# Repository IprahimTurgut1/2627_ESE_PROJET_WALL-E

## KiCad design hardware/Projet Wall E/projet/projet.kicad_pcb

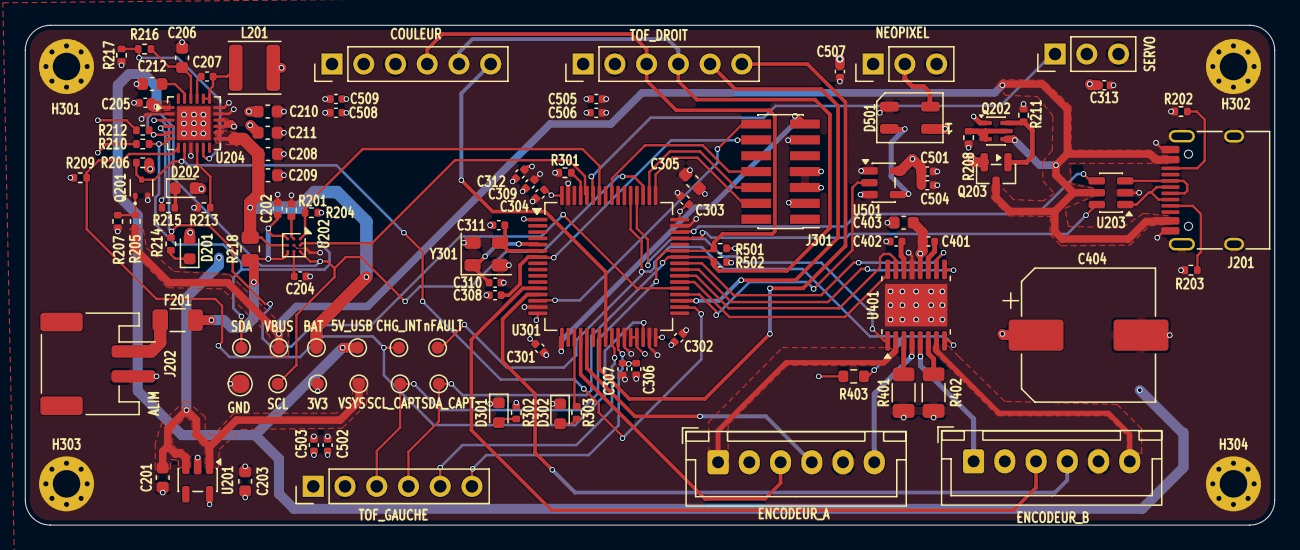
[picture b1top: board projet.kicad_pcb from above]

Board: 4 copper layers, 100.0 x 40.0 mm, 108 parts (0 on the bottom side), 75 nets.

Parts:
3V3: +3.3V; TestPoint_Pad_D1.0mm
5V_USB: +5V_USB; TestPoint_Pad_D1.0mm
BAT: BAT; TestPoint_Pad_D1.0mm
C201, C203, C208, C209, C210, C211, C212, C403: 10u; C_0603_1608Metric
C202, C205, C307, C312, C313: 1u; C_0402_1005Metric
C204: 2u2; C_0402_1005Metric
C206, C305: 4u7; C_0603_1608Metric
C207: 47n; C_0402_1005Metric
C301, C302, C303, C304, C308, C309, C501, C504, C507: 100n; C_0402_1005Metric
C306, C401: 10n; C_0402_1005Metric
C310, C311: 10p; C_0402_1005Metric
C402: 2.2uF; C_0402_1005Metric
C404: 470u/25V; CP_Elec_10x10.5
C502, C505, C508: 100nF; C_0402_1005Metric
C503, C506, C509: 10uF; C_0402_1005Metric
CHG_INT: CHG_INT; TestPoint_Pad_D1.0mm
COULEUR: Conn_01x06; PinHeader_1x06_P2.54mm_Vertical
D201, D202: LED; LED_0603_1608Metric
D301: POWER; LED_0603_1608Metric
D302: STATUS; LED_0603_1608Metric
D501: WS2812B; LED_WS2812B-Mini_PLCC4_3.5x3.5mm
ENCODEUR_A: Conn_01x06; JST_XH_B6B-XH-A_1x06_P2.50mm_Vertical
ENCODEUR_B: Conn_01x06; JST_XH_B6B-XH-A_1x06_P2.50mm_Vertical
F201: Fuse; Fuse_1206_3216Metric
GND: GND; TestPoint_Pad_D1.5mm
H301, H302, H303, H304: MountingHole_Pad; MountingHole_2.2mm_M2_Pad_Via
J201: USB_C_Receptacle_USB2.0_16P; USB_C_Receptacle_HRO_TYPE-C-31-M-12
J202: Conn_01x02; JST_PH_S2B-PH-SM4-TB_1x02-1MP_P2.00mm_Horizontal
J301: Conn_ST_STDC14; PinHeader_2x07_P1.27mm_Vertical_SMD
L201: 1u; L_Sunlord_SWPA4030S
NEOPIXEL: Conn_01x03; PinHeader_1x03_P2.54mm_Vertical
Q201: 2SK3019; SOT-523
Q202: MMDT5401; SOT-363_SC-70-6
Q203: DMP3099L; SOT-23
R201, R204, R206, R207, R216, R217, R301: 10k; R_0402_1005Metric
R202, R203: 5k1; R_0402_1005Metric
R205: 100; R_0402_1005Metric
R208, R211: 100k; R_0402_1005Metric
R209: 4k7; R_0402_1005Metric
R210, R212: 1.5k; R_0402_1005Metric
R213: 470; R_0402_1005Metric
R214, R215: 2k2; R_0402_1005Metric
R218: 10m; R_0805_2012Metric
R302, R303: 1k; R_0402_1005Metric
R401, R402: 200m; R_1206_3216Metric
R403: 10k; R_0603_1608Metric
R501, R502: 4.7k; R_0402_1005Metric
SCL: SCL; TestPoint_Pad_D1.0mm
SCL_CAPT: SCL_CAPT; TestPoint_Pad_D1.0mm
SDA: SDA; TestPoint_Pad_D1.0mm
SDA_CAPT: SDA_CAPT; TestPoint_Pad_D1.0mm
SERVO: Conn_01x03; PinHeader_1x03_P2.54mm_Vertical
TOF_DROIT: Conn_01x06; PinHeader_1x06_P2.54mm_Vertical
TOF_GAUCHE: Conn_01x06; PinHeader_1x06_P2.54mm_Vertical
U201: AP2112K-3.3; SOT-23-5
U202: BQ27220YZFR; Texas_DSBGA-9_1.62x1.58mm_Layout3x3_P0.5mm
U203: USBLC6-2SC6; SOT-23-6
U204: BQ25896RTW; Texas_RTW_WQFN-24-1EP_4x4mm_P0.5mm_EP2.7x2.7mm_ThermalVias
U301: STM32G431RBTx; LQFP-64_10x10mm_P0.5mm
U401: DRV8833PWP; HTSSOP-16-1EP_4.4x5mm_P0.65mm_EP3.4x5mm_Mask2.46x2.31mm_The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
U501: SN74AHCT1G125DBVR; SOT-23-5
VBUS: VBUS; TestPoint_Pad_D1.0mm
VSYS: VSYS; TestPoint_Pad_D1.0mm
Y301: 16MHz; Crystal_SMD_EuroQuartz_MT-4Pin_3.2x2.5mm
nFAULT: MOT_nFAULT; TestPoint_Pad_D1.0mm

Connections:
+3.3V: 3V3.1 (1_1), C203.1, C301.1, C302.1, C303.1, C304.1, C305.1, C306.1, C307.1, C309.1, C312.1, C502.1, C503.1, C505.1, C506.1, C508.1, C509.1, COULEUR.1, ENCODEUR_A.2, ENCODEUR_B.2, J301.3 (VCC), R204.2, R209.1, R210.1, R212.1, R302.1, R403.2, R501.1, R502.1, TOF_DROIT.1, TOF_GAUCHE.1, U201.5 (VOUT), U301.1 (VBAT), U301.16 (VDD), U301.28 (VREF+), U301.29 (VDDA), U301.32 (VDD), U301.48 (VDD), U301.64 (VDD)
+5V_USB: 5V_USB.1 (1_1), C205.1, C313.1, C401.1, C403.1, C404.1, C501.1, C504.2, C507.1, D501.1 (VDD), NEOPIXEL.1, Q202.1 (E1), Q203.2 (S), SERVO.2, U204.1 (VBUS), U401.12 (VM), U501.5 (VCC)
/Alimentation/BAT: BAT.1 (1_1), C208.2, C209.2, R218.2, U202.C2 (SRN), U204.13 (BAT), U204.14 (BAT)
/Alimentation/CHG_INT: CHG_INT.1 (1_1), R209.2, U204.7 (INT), U301.30 (PB10)
/Alimentation/CHG_OTG: Q201.3 (D), R206.2, U204.8 (OTG), U301.34 (PB12)
/Alimentation/CHG_PG: R214.2, U204.3 (~PG), U301.37 (PB15)
/Alimentation/GAUGE_INT: R204.1, U202.A1 (GPOUT), U301.58 (PB5)
/Alimentation/PACKP: C202.1, F201.1, R218.1, U202.C1 (SRP), U202.C3 (BAT)
/Alimentation/SCL: R212.2, SCL.1 (1_1), U202.A3 (SCL), U204.5 (SCL), U301.51 (PA15)
/Alimentation/SDA: R210.2, SDA.1 (1_1), U202.A2 (SDA), U204.6 (SDA), U301.60 (PB7)
/Alimentation/USB_DM: U203.6 (I/O1), U301.45 (PA11)
/Alimentation/USB_DP: U203.4 (I/O2), U301.46 (PA12)
/Capteur/APDS_INT: COULEUR.6, U301.24 (PB0)
/Capteur/NEOPIXEL: U301.36 (PB14), U501.2
/Capteur/NP_5V: D501.4 (DIN), U501.4
/Capteur/SCL_CAPT: COULEUR.4, R501.2, SCL_CAPT.1 (1_1), TOF_DROIT.3, TOF_GAUCHE.3, U301.43 (PA9)
/Capteur/SDA_CAPT: COULEUR.5, R502.2, SDA_CAPT.1 (1_1), TOF_DROIT.4, TOF_GAUCHE.4, U301.42 (PA8)
/Capteur/TOF_L_GPIO1: TOF_GAUCHE.5, U301.25 (PB1)
/Capteur/TOF_L_XSHUT: TOF_GAUCHE.6, U301.26 (PB2)
/Capteur/TOF_R_GPIO1: TOF_DROIT.5, U301.35 (PB13)
/Capteur/TOF_R_XSHUT: TOF_DROIT.6, U301.23 (PC5)
/MCU/BOOT0: R301.2, U301.61 (PB8)
/MCU/ENCA_AOUT: ENCODEUR_A.3, U301.20 (PA6)
/MCU/ENCA_BOUT: ENCODEUR_B.3, U301.12 (PA0)
/MCU/ENCB_AOUT: ENCODEUR_A.4, U301.21 (PA7)
/MCU/ENCB_BOUT: ENCODEUR_B.4, U301.13 (PA1)
/MCU/LED_STATUS: R303.1, U301.19 (PA5)
/MCU/MOT_AIN1: U301.38 (PC6), U401.16 (AIN1)
/MCU/MOT_AIN2: U301.39 (PC7), U401.15 (AIN2)
/MCU/MOT_BIN1: U301.40 (PC8), U401.9 (BIN1)
/MCU/MOT_BIN2: U301.41 (PC9), U401.10 (BIN2)
/MCU/MOT_nFAULT: R403.1, U301.53 (PC11), U401.8 (~FAULT), nFAULT.1 (1_1)
/MCU/MOT_nSLEEP: U301.52 (PC10), U401.1 (~SLEEP)
/MCU/NRST: C308.1, J301.12 (~RST), U301.7 (PG10)
/MCU/SERVO_PWM: SERVO.1, U301.59 (PB6)
/MCU/SWCLK: J301.6 (JCLK/SWCLK), U301.50 (PA14)
/MCU/SWDIO: J301.4 (JTMS/SWDIO), U301.49 (PA13)
/MCU/SWO: J301.8 (JTDO/SWO), U301.56 (PB3)
/MCU/VCP_RX: J301.13 (VCP_RX), U301.17 (PA3)
/MCU/VCP_TX: J301.14 (VCP_TX), U301.14 (PA2)
/Moteur/AOUT1: ENCODEUR_A.1, U401.2 (AOUT1)
/Moteur/AOUT2: ENCODEUR_A.6, U401.4 (AOUT2)
/Moteur/BOUT1: ENCODEUR_B.6, U401.7 (BOUT1)
/Moteur/BOUT2: ENCODEUR_B.1, U401.5 (BOUT2)
GND: C201.2, C202.2, C203.2, C204.2, C205.2, C206.1, C208.1, C209.1, C210.1, C211.1, C212.1, C301.2, C302.2, C303.2, C304.2, C305.2, C306.2, C307.2, C308.2, C309.2, C310.1, C311.1, C312.2, C313.2, C402.1, C403.2, C404.2, C501.2, C502.2, C503.2, C504.1, C505.2, C506.2, C507.2, C508.2, C509.2, COULEUR.3, D301.1 (K), D302.1 (K), D501.3 (VSS), ENCODEUR_A.5, ENCODEUR_B.5, GND.1 (1_1), H301.1 (1_1), H302.1 (1_1), H303.1 (1_1), H304.1 (1_1), J201.A1 (GND), J201.A12 (GND), J201.B1 (GND), J201.B12 (GND), J201.SH (SHIELD), J202.2, J301.5 (GND), J301.7 (GND), J301.11 (GNDDetect), NEOPIXEL.3, Q201.2 (S), R201.2, R202.2, R203.2, R207.2, R208.2, R211.2, R213.2, R217.2, R301.1, R401.1, R402.1, SERVO.3, TOF_DROIT.2, TOF_GAUCHE.2, U201.2 (GND), U202.B2 (V_{SS}), U203.2 (GND), U204.2 (PSEL), U204.9 (~CE), U204.17 (PGND), U204.18 (PGND), U204.25 (PGND), U301.15 (VSS), U301.27 (VSSA), U301.31 (VSS), U301.47 (VSS), U301.63 (VSS), U401.13 (GND), U401.17 (GND), U501.1, U501.3 (GND), Y301.2 (G), Y301.4 (G)
unnamed: C207.2, L201.1, U204.19 (SW), U204.20 (SW)
unnamed: D201.1 (K), R214.1
unnamed: D202.1 (K), R215.1
unnamed: D301.2 (A), R302.2
unnamed: D302.2 (A), R303.2
unnamed: D501.2 (DOUT), NEOPIXEL.2
unnamed: J201.A5 (CC1), R203.1
unnamed: J201.B5 (CC2), R202.1
unnamed: J201.A6 (D+), J201.B6 (D+), U203.3 (I/O2)
unnamed: J201.A7 (D-), J201.B7 (D-), U203.1 (I/O1)
unnamed: F201.2, J202.1
unnamed: Q201.1 (G), R205.2, R207.1
unnamed: Q202.2 (B1), Q202.3 (C2), Q202.5 (B2), R208.1
unnamed: Q202.6 (C1), Q203.1 (G), R211.1
unnamed: R201.1, U202.B1 (BIN)
unnamed: C204.1, U202.B3 (V_{DD})
unnamed: C207.1, U204.21 (BTST)
unnamed: R213.1, U204.10 (ILIM)
unnamed: C212.2, U204.23 (PMID)
unnamed: C206.2, R216.2, U204.22 (REGN)
unnamed: R215.2, U204.4 (STAT)
unnamed: R216.1, R217.1, U204.11 (TS)
unnamed: C310.2, U301.5 (PF0), Y301.1
unnamed: C311.2, U301.6 (PF1), Y301.3
unnamed: R401.2, U401.3 (AISEN)
unnamed: R402.2, U401.6 (BISEN)
unnamed: C401.2, U401.11 (VCP)
unnamed: C402.2, U401.14 (VINT)
VBUS: J201.A4 (VBUS), J201.A9 (VBUS), J201.B4 (VBUS), J201.B9 (VBUS), Q202.4 (E2), Q203.3 (D), R205.1, U203.5 (VBUS), VBUS.1 (1_1)
VSYS: C201.1, C210.2, C211.2, D201.2 (A), D202.2 (A), L201.2, R206.1, U201.1 (VIN), U201.3 (EN), U204.15 (SYS), U204.16 (SYS), VSYS.1 (1_1)

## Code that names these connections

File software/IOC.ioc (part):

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Mcu.Name=STM32G431R(6-8-B)Tx
Mcu.Package=LQFP64
Mcu.UserName=STM32G431RBTx
PA0.GPIOParameters=GPIO_Label
PA0.GPIO_Label=ENCA_BOUT
PA0.Signal=S_TIM2_CH1
PA1.GPIOParameters=GPIO_Label
PA1.GPIO_Label=ENCB_BOUT
PA1.Signal=S_TIM2_CH2
PA11.Mode=Device
PA11.Signal=USB_DM
PA12.Mode=Device
PA12.Signal=USB_DP
PA13.GPIOParameters=GPIO_Label
PA13.GPIO_Label=T_SWDIO
PA13.Mode=Trace_Asynchronous_SW
PA13.Signal=SYS_JTMS-SWDIO
PA14.GPIOParameters=GPIO_Label
PA14.GPIO_Label=T_SWCLK
PA14.Mode=Trace_Asynchronous_SW
PA14.Signal=SYS_JTCK-SWCLK
PA15.Mode=I2C
PA15.Signal=I2C1_SCL
PA2.GPIOParameters=GPIO_Label
PA2.GPIO_Label=VCP_TX
PA2.Mode=Asynchronous
PA2.Signal=USART2_TX
PA3.GPIOParameters=GPIO_Label
PA3.GPIO_Label=VCP_RX
PA3.Mode=Asynchronous
PA3.Signal=USART2_RX
PA5.GPIOParameters=GPIO_Label
PA5.GPIO_Label=LED_STATUS
PA5.Signal=GPIO_Output
PA6.GPIOParameters=GPIO_Label
PA6.GPIO_Label=ENCA_AOUT
PA6.Signal=S_TIM3_CH1
PA7.GPIOParameters=GPIO_Label
PA7.GPIO_Label=ENCB_AOUT
PA7.Signal=S_TIM3_CH2
PA8.Mode=I2C
PA8.Signal=I2C2_SDA
PA9.Mode=I2C
PA9.Signal=I2C2_SCL
PB0.GPIOParameters=GPIO_Label
PB0.GPIO_Label=APDS_INT
PB0.Signal=GPXTI0
PB1.GPIOParameters=GPIO_Label
PB1.GPIO_Label=TOF_L_GPIO1
PB1.Signal=GPIO_Input
PB10.GPIOParameters=GPIO_Label
PB10.GPIO_Label=CHG_INT
PB10.Signal=GPXTI10
PB12.GPIOParameters=GPIO_Label
PB12.GPIO_Label=CHG_OTG
PB12.Signal=GPIO_Input
PB13.GPIOParameters=GPIO_Label
PB13.GPIO_Label=TOF_R_GPIO1
PB13.Signal=GPIO_Input
PB14.GPIOParameters=GPIO_Label
PB14.GPIO_Label=NEOPIXEL
PB14.Signal=S_TIM15_CH1
PB15.GPIOParameters=GPIO_Label
PB15.GPIO_Label=CHG_PG
PB15.Signal=GPIO_Input
PB2.GPIOParameters=GPIO_Label
PB2.GPIO_Label=TOF_L_XSHUT
PB2.Signal=GPIO_Output
PB3.GPIOParameters=GPIO_Label
PB3.GPIO_Label=T_SWO
PB3.Mode=Trace_Asynchronous_SW
PB3.Signal=SYS_JTDO-SWO
PB5.GPIOParameters=GPIO_Label
PB5.GPIO_Label=GAUGE_INT
PB5.Signal=GPXTI5
PB6.GPIOParameters=GPIO_Label
PB6.GPIO_Label=SERVO_PWM
PB6.Signal=S_TIM4_CH1
PB7.Mode=I2C
PB7.Signal=I2C1_SDA
PC10.GPIOParameters=GPIO_Label
PC10.GPIO_Label=MOT_nSLEEP
PC10.Signal=GPIO_Output
PC11.GPIOParameters=GPIO_Label
PC11.GPIO_Label=MOT_nFAULT
PC11.Signal=GPIO_Input
PC5.GPIOParameters=GPIO_Label
PC5.GPIO_Label=TOF_R_XSHUT
PC5.Signal=GPIO_Output
PC6.GPIOParameters=GPIO_Label
PC6.GPIO_Label=MOT_AIN1
PC6.Signal=S_TIM8_CH1
PC7.GPIOParameters=GPIO_Label
PC7.GPIO_Label=MOT_AIN2
PC7.Signal=S_TIM8_CH2
PC8.GPIOParameters=GPIO_Label
PC8.GPIO_Label=MOT_BIN1
PC8.Signal=S_TIM8_CH3
PC9.GPIOParameters=GPIO_Label
PC9.GPIO_Label=MOT_BIN2
PC9.Signal=S_TIM8_CH4
PF0-OSC_IN.GPIOParameters=GPIO_Label
PF0-OSC_IN.GPIO_Label=RCC_OSC_IN
PF0-OSC_IN.Mode=HSE-External-Oscillator
PF0-OSC_IN.Signal=RCC_OSC_IN
PF1-OSC_OUT.GPIOParameters=GPIO_Label
PF1-OSC_OUT.GPIO_Label=RCC_OSC_OUT
PF1-OSC_OUT.Mode=HSE-External-Oscillator
PF1-OSC_OUT.Signal=RCC_OSC_OUT
RCC.HSE_VALUE=16000000
RCC.SYSCLKFreq_VALUE=170000000
RCC.SYSCLKSource=RCC_SYSCLKSOURCE_PLLCLK
board=NUCLEO-G431RB
boardIOC=true
